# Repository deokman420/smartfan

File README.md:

<h1 align="center">Smartfan</h1>

<p align="center">
  <b>A bathroom fan that knows when to run.</b><br>
  It switches your extractor fan on for light, humidity and odor, runs it until the room is
  actually dry, and then stops. Open source, on a Raspberry Pi Pico 2 W.
</p>

https://github.com/user-attachments/assets/ac6792f2-4697-47a9-bf49-5d41668e7b6c

<p align="center">If the video does not play here, the same walkthrough is in the <a href="https://phbeks.com/blog/smartfan-launch.html">launch write-up</a>.</p>

<p align="center">
  <a href="https://smartfan.phbeks.com"><b>Website</b></a> ·
  <a href="https://smartfan.phbeks.com/demo/"><b>Live demo</b></a> ·
  <a href="https://smartfan.phbeks.com/kb/"><b>Docs</b></a> ·
  <a href="https://my.home-assistant.io/redirect/hacs_repository/?owner=deokman420&repository=smartfan&category=integration"><b>Add to Home Assistant</b></a>
</p>

<p align="center">

</p>

<table>
  <tr>
    <td width="72%"></td>
    <td width="28%"></td>
  </tr>
</table>

<p align="center"><sub>The app, served by the fan itself. <a href="https://smartfan.phbeks.com/demo/">Try it in your browser</a>. The demo starts from four days of real data and simulates a fan from there.</sub></p>

---

## Why another fan controller?

Fixed thresholds don't work in a bathroom.

- **Humidity:** a muggy August day sits at 65 % RH on its own, and a fan set to
  "on above 60 %" never stops. Smartfan learns a slow **baseline** for your room
  and reacts to the **rise** above it.
- **Light:** measured in this room, direct sun reads 85 % of the sensor's range
  and the ceiling lamp 81 %. Daylight is brighter than the bulb, so no level can
  tell them apart. Speed can: the lamp moves the reading 51,511 counts in one
  2-second sample, and the sky never managed more than 51. Smartfan watches for
  that **step**, so sunlight never starts the fan.
- **Odor:** a Sensirion SGP41 reports raw counts with no absolute meaning, and
  they drift with humidity and age. Smartfan learns the room's normal air,
  corrects for humidity, and runs the fan when that changes, **even after the
  light is off**. Then it stops.

A few commercial fans sense odor too. None we found say how theirs decides when
to start or stop. Smartfan's logic is [written down](https://smartfan.phbeks.com/kb/how-it-works/)
and in this repo.

## What it does

|  |  |
|---|---|
| **Runs itself** | Light, humidity and odor start the fan. Humidity decides how long it runs. Run caps stop it running for ever, and stall detection notices a fan that isn't turning. |
| **Its own app, no cloud** | The fan serves its app from its own flash at `http://fan.local/`, with a week of history stored on the board. No account, no server, no broker required. |
| **Home Assistant** | A HACS integration, or MQTT with discovery. Every reading, threshold and control becomes an entity, with a ready-made dashboard. |
| **Signed updates over the air** | Only your build machine can update it, and a bad update rolls itself back. The recovery files only travel over USB. |
| **A button and two lights** | Boost, relearn and Wi-Fi setup all work with no app and no network. |

## In Home Assistant

Add the integration with HACS (custom repository), then add the fan by its
address, `fan.local`. Or point the fan at your MQTT broker and it appears
through discovery. Full guide: [Networking and Home Assistant](https://smartfan.phbeks.com/kb/networking/).

## The hardware

<table>
  <tr>
    <td width="50%"></td>
    <td width="50%"></td>
  </tr>
  <tr>
    <td><b>V1, the bench unit.</b> Running and commissioned in a real bathroom. 5 V USB, no mains anywhere.</td>
    <td><b>V2, the ceiling unit.</b> Designed, not built yet. <a href="https://smartfan.phbeks.com/model/">Explore it in 3D</a>.</td>
  </tr>
</table>

| V1 part | |
|---|---|
| Board | Raspberry Pi Pico 2 W (RP2350), MicroPython 1.29.0 |
| Humidity and temperature | DHT22 |
| Odor | Sensirion SGP41 (VOC and NOx), I²C |
| Light | LDR in a divider against 10 kΩ |
| Fan | Noctua NF-A4x10 5V, 3-wire with tachometer |
| Switching | S8050 NPN, low side |
| Controls | Green and red LEDs, one push button |

Parts, wiring, the pin map and the V2 board are in [Build your own](https://smartfan.phbeks.com/kb/build/).

> [!WARNING]
> **The V2 build in [`hardware/v2/`](hardware/v2/) connects to mains voltage.**
> Mains wiring can kill you and can start a fire. Build it only if you are
> competent to work on mains, keep it unplugged while it is open, and follow
> your local electrical code, which may require a licensed electrician for a
> fixed ceiling installation. The V2 board has **not been fabricated or tested
> yet**. It is a design to check, not a proven build. V1 runs on 5 V USB. This
> project comes with **no warranty** (see [License](#license)).

## Quick start (V1)

You need Python 3 with `pip install mpremote`, Node.js 20+, and a USB cable.
The examples use `COM5`; on Linux or macOS it's something like `/dev/ttyACM0`.

1. **Flash MicroPython**, the Pico 2 W ARM build from
   <https://micropython.org/download/RPI_PICO2_W/>. Hold BOOTSEL, plug in, and
   drag the `.uf2` onto the drive.
2. **Copy the firmware** in safe mode, so the controller and its 8 s watchdog
   aren't running while files land:

   ```bash
   mpremote connect COM5 fs touch :safemode + reset
   mpremote connect COM5 fs cp boot.py ota.py main.py config.py settings.py \
     telemetry.py light.py sgp41.py sht4x.py voc.py net.py mqtt.py ringbuf.py \
     calibrate.py provision.py improv.py httpd.py webapi.py store.py wifi.py :
   ```

   Don't copy `secrets.py`, `settings.json` or `identity.py` from a working
   copy. They belong to one device.
3. **Build and push the app.** This also takes the board out of safe mode:

   ```bash
   cd app && npm ci && cd ..
   python tools/build_www.py --push COM5
   ```

4. **Connect it to Wi-Fi.** With no `secrets.py` the board opens its own setup
   network. See [Set up a unit](https://smartfan.phbeks.com/kb/setup/).
5. **Calibrate the light** in the room it will live in, then optionally add it
   to Home Assistant.

After that, firmware updates go over the air. See
[Updating over the air](https://smartfan.phbeks.com/kb/ota/).

## How it works

| State | Lights | |
|---|---|---|
| LEARN | green blinking | The first 60 s, building the humidity baseline |
| IDLE | green solid | Watching, fan off |
| RUN | red solid | Fan on for light, humidity or odor |
| BOOST | red blinking | A manual 15-minute run |
| FAULT | alternating | A sensor went silent, or the fan isn't turning |

A short press of the button boosts for 15 minutes or clears a fault. Hold it
for two seconds to relearn every baseline, or eight seconds to open the Wi-Fi
setup window.

The control logic, what a real shower looks like, and the field
measurements behind each threshold are in [How it works](https://smartfan.phbeks.com/kb/how-it-works/).

## Documentation

| | |
|---|---|
| [Build your own](https://smartfan.phbeks.com/kb/build/) | Parts, wiring, pin map, first install |
| [Set up a unit](https://smartfan.phbeks.com/kb/setup/) | Wi-Fi provisioning, naming, calibration |
| [Networking and Home Assistant](https://smartfan.phbeks.com/kb/networking/) | The fan's own server, MQTT, the dashboard |
| [Updating over the air](https://smartfan.phbeks.com/kb/ota/) | Signed OTA, and why it can't brick the board |
| [How it works](https://smartfan.phbeks.com/kb/how-it-works/) | States, control logic, a real shower |
| [Odor sensing with the SGP41](https://smartfan.phbeks.com/kb/sgp41-odor-sensing/) | The signal, its sign, and settling time |
| [Daylight is brighter than the bulb](https://smartfan.phbeks.com/kb/daylight-is-brighter-than-the-bulb/) | Why light is found by its step, not its level |
| [Files in the repo](https://smartfan.phbeks.com/kb/files/) | What each file does |
| [Roadmap](https://smartfan.phbeks.com/kb/roadmap/) | The phases so far, the ceiling unit and multi-room next |

The same pages are in [`docs/`](docs/) if you'd rather read them here.

## Repository layout

| Path | What's in it |
|---|---|
| `*.py` (root) | The MicroPython firmware: control loop, sensors, Wi-Fi, HTTP API, OTA |
| [`app/`](app/) | The Svelte app the fan serves, plus the public demo build |
| [`custom_components/smartfan/`](custom_components/smartfan/) | The Home Assistant integration |
| [`hardware/`](hardware/) | V2 schematic, PCB and printed parts (build123d scripts and STLs) |
| [`tools/`](tools/) | Build, flash, OTA publishing and dashboard scripts |
| [`tests/`](tests/) | Regression suites, from host-only checks to hardware and HA |
| [`docs/`](docs/), [`site/`](site/) | The knowledge base and the website at smartfan.phbeks.com |

## Contributing

Issues and pull requests are welcome. Before opening a pull request:

- Run the host-only suites listed in [`tests/README.md`](tests/README.md). They
  need no board.
- Write in American English (color, not colour), in code, docs and UI text.
- Keep a behavior change and its doc change in the same commit. The docs live
  in this repo for that reason.

## License

- **Firmware, app, Home Assistant integration and tools:** GNU GPL v3.0. See
  [`LICENSE`](LICENSE).
- **Hardware** (everything in [`hardware/`](hardware/): schematic, PCB,
  Gerbers, CAD scripts and STLs): CERN Open Hardware Licence v2, Strongly
  Reciprocal. See [`hardware/LICENSE`](hardware/LICENSE).
- **Bundled third-party files** keep their own licenses: Inter and JetBrains
  Mono (SIL Open Font License, [`app/LICENSES/`](app/LICENSES/)) and three.js
  (MIT, [`hardware/v2/cad/vendor/LICENSE-three.txt`](hardware/v2/cad/vendor/LICENSE-three.txt)).

Both licenses come with no warranty. You build and install this at your own
risk, and that matters most for anything connected to mains.

<p align="center"><sub>Made by <a href="https://phbeks.com">phbeks.com</a></sub></p>

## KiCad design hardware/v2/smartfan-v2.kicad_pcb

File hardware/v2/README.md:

# Smartfan V2 board

> [!WARNING]
> **Not fabricated, not tested, and it carries mains.** Nothing here has been built yet. Check every footprint against parts in hand (see "Before fab" below) before ordering, and do not power it from mains unless you are competent to work on mains. Licensed under CERN-OHL-S v2 ([`../LICENSE`](../LICENSE)), with no warranty.

Schematic and PCB for prototype V2: one Noctua NF-F12, a Pico 2 W, and an SHT40. This is not the two-fan V2.2 board. The circuit is described in `hardware/v2/prototype-v2.md`, `hardware/v2/build-sheet-v2.html` and `hardware/v2/wiring-v2.html`. The board changed that circuit in three ways, listed under "Changed on 2026-11-08", and those files were brought in line on 2026-11-09. Where they disagree with this README, this README wins.

Open `smartfan-v2.kicad_pro` in KiCad 10. `generate.py` is the source. It rewrites the schematic and the board. Run it with KiCad's Python:

```
& "$env:LOCALAPPDATA\Programs\KiCad\10.0\bin\python.exe" hardware/v2/generate.py
```

Do not hand-edit `smartfan-v2.kicad_sch`, `smartfan-v2.kicad_pcb` or `smartfan-v2.kicad_dru`.

The run checks itself and stops on the first problem:

1. The netlist KiCad reads from the drawn schematic must match `PARTS` pin for pin, the off-board parts included.
2. ERC. The only findings allowed are `lib_symbol_mismatch` warnings, because the symbols are embedded, renamed copies.
3. DRC with schematic parity. It has to come back empty.

Then it rewrites `smartfan-v2-schematic.pdf`, `smartfan-v2-front.svg` (front copper and silk), `smartfan-v2-back.svg` (back copper, same orientation as the front, so the ground pour and the +12 V / +5 V runs are visible) and everything in `fab/`. On 2026-11-08 in KiCad 10.0.5: 24 `lib_symbol_mismatch` warnings, DRC clean, parity clean.

`fab/` holds the Gerbers and the drill files. Two layers, 1.6 mm, 1 oz copper. The plot origin is the lower-left corner of the outline, in millimeters, and the coordinates are positive. The plated holes, and the one via, are in `smartfan-v2-PTH.drl`. `smartfan-v2-NPTH.drl` has the MOSFET tab hole (3.5 mm) and the fan header's locating peg (1.1 mm). The four mounting holes are unplated 3.2 mm circles in `smartfan-v2-Edge_Cuts.gm1`, not in the drill file. The back silkscreen is empty.

## Mains

120 V lands in J5, a Phoenix MKDS 1,5/2-5,08 screw terminal (1715721) beside the IRM-10's AC pins. Its wire entries face the mains end wall. Pin 1 takes the C8's unfused lead. Pin 2 takes the lead from the fuse holder. The C8 is not polarized, so "hot" means whichever lead the fuse is in. The silk says C8 and FUSE. The IEC C8 and the fuse holder are panel parts. They are on the schematic and not on the board.

There is no earth. Do not bond 0 V or the MOSFET tab to the box. The tab is the drain: use no screw in it, or a nylon one. If the module marks and the schematic disagree on which pin is +12 V, follow the module.

120 V copper keeps 6.4 mm from everything that is not 120 V. That is more than reinforced insulation needs at 120 V, and enough at 230 V.

- The DRC rule in `smartfan-v2.kicad_dru` enforces it as both clearance and creepage. It covers low-voltage copper, the ground pour, and pads with no net.
- DRC checks one copper layer at a time. `generate.py` also keeps 6.4 mm between layers, which DRC does not check.
- The closest approach is 6.50 mm, between the fused lead and the back ground pour.
- Line to neutral is 2.48 mm at J5's own pads and 3 mm or more elsewhere.
- A screw head or hex standoff at the nearest mounting hole is 8.3 mm from 120 V copper.

## Before fab

None of this has been checked against parts in hand. Do it before ordering.

1. **Wi-Fi in a closed aluminum box.** An unpainted die-cast 1590BB with the lid on is close to a shielded can. The Pico's only antenna is on the module, and the whole unit runs over Wi-Fi: MQTT, Home Assistant and OTA. Put a running Pico W, or a phone, in the box with the lid screwed down, and read the signal from the router or `/api/state`. If it drops out, the fix is a plastic lid or a plastic window over the antenna. That changes the box, not the board, but it decides whether this box is the right one. The board keeps all copper off both layers under the antenna and for 7 mm past the end of the module.
2. **Caliper the box.** The 96 × 70 mm outline uses Hammond's drawing figures: a flat of 103.50 × 78.00 mm between the corner bosses and a 29.75 mm inner height. Stacking 21.5 mm for the IRM-10 and 1.6 mm of board leaves 6.6 mm for standoffs with nothing to spare. Use 5 or 6 mm nylon standoffs.
3. **Insulate under the board.** The 120 V solder joints face the aluminum floor about 4 mm away. Lay a 0.4 mm polycarbonate or fish-paper sheet under the board, and trim the AC leads short.
4. **Panel parts against the board.** The C8 inlet and the fuse holder reach roughly 20–35 mm into the box from the mains end wall. The board covers most of the floor, and the IRM-10 at that end is 21.5 mm tall. Check, with the parts in the box, that neither one lands on the module or on J5's screws.
5. **Print the board 1:1 and lay the parts on it.** Check the IRM-10 pins, the R-78E, J5, the keyed fan header, and the Pico sockets.
6. **USB faces the mains end.** The build sheet puts a USB slot in the far wall, but on this board the Pico's USB end is at the mains end, beside J5. With the board in the box, unplug the cord, take the lid off, and use a right-angle micro-USB lead, or lift the Pico out of its sockets. The `www/` bundle only goes over USB.

## Changed on 2026-11-08

- **J5, the mains terminal**, is new. Before, the C8 and fuse leads were to be soldered to the IRM-10's pins on the underside, with no strain relief and facing the floor. The mounting hole at (12, 34) moved to (22, 33.5) to make room.
- **J2 is a keyed 4-pin fan header** (`FanPinHeader_1x04`; Molex 47053-1000 or any 4-pin PWM fan header). A bare pin header let the fan plug go on backwards. That puts switched 12 V on the fan's tach output and the fan's ground on +5 V.
- **The LED resistors moved to the anode side**, and **R9, 1 kΩ, is new** in series with the button. R7, R8 and R9 now sit between J4 and the Pico. A pinched grille cable, or a static spark at the button, now meets a resistor before it meets a GPIO. J4's pinout is unchanged; pins 4 and 6 are ground on the board.
- **The fan switch was regrouped** around Q1:
  - R4 runs from gate to source on the left of Q1.
  - R3 drops straight from the gate to Q2's collector.
  - R1 and R2 meet the base from below and above.
  - D2 hangs off the yellow lead.
  - R5 sits over the tach pin.
  - J4 moved beside J2.

  The holes at (80, 32) and (76, 50) moved to (80, 36.5) and (91, 63). Every net in that corner is a short hand route. The tach line crosses the fan line on the back and comes up through one via. The old board's router walked BASE 120 mm, FAN_ON 118 mm and LIGHT 317 mm. Now they are 24, 7 and 44 mm.
- **R6** sits beside J3, so the LDR line no longer crosses the board.
- **Net names and footprint library names** on the board now match the schematic. "Update PCB from Schematic" no longer renames every net or swaps every footprint.
- **The schematic** joins the Pico by labels instead of long wires, places every reference and value clear of wires, and marks junctions.

## Wiring the connectors

J2 is the NF-F12, pin 1 at the square pad. The keying wall faces the board edge. The silk names each lead's color.

1. Black, permanent 0 V. Do not low-side switch it.
2. Yellow, IRF9540 drain, switched +12 V. Never a GPIO.
3. Green, open-collector tach to GP18, pulled up to Pico 3V3 only.
4. Blue, +5 V from the buck, before the 1N5819. Never 12 V and never VSYS. A low PWM pin stops the fan even with 12 V on yellow.

These are not the V1 lead colors. On the V1 NF-A4x10, yellow was tach.

J3 is the grille sensor cable, six pins: 1 GND, 2 3V3, 3 SDA (GP0), 4 SCL (GP1), 5 LDR, 6 3V3 for the LDR. Pull-ups are on the SHT40. R6 stays on the board. SGP41 is not on this board. GP22 is free. The DHT22 does not come across.

J4 is the button and LED cable, six pins: 1 GND, 2 button, 3 green anode, 4 green cathode, 5 red anode, 6 red cathode. The button reaches GP16 through R9, the green LED GP19 through R7, the red LED GP20 through R8. The button, both LEDs, the LDR and the SHT40 are on the grille, not on this board.

J5 is mains: pin 1 the C8's unfused lead, pin 2 from the fuse.

## The rest

- The Pico sits in two 20-pin sockets. The footprint assumes it, and traces run under the module.
- VBUS, pin 40, gets no wire. Installed power is the buck into VSYS, pin 39, through the 1N5819. The band is the cathode at VSYS. With the cord in and USB unplugged, pin 39 should read about 4.5–4.8 V.
- GP17 high turns the fan on. R1, 1 kΩ, is the base resistor. R2, 100 kΩ, holds the base down while GP17 floats at boot. Do not swap them. The S8050 flat face, left to right, is E-B-C. Diode-test it before soldering.
- The Recom R-78E5.0-1.0 uses the 0.5 A footprint. The pin pitch matches. The body is 11.6 × 8.5 × 10.4 mm. Its datasheet needs no external capacitors; 10 µF on the input is only part of its EMC filter.
- The grille parts are drawn off the board and connect through J3 and J4. On the schematic, labels with the same name are one net.

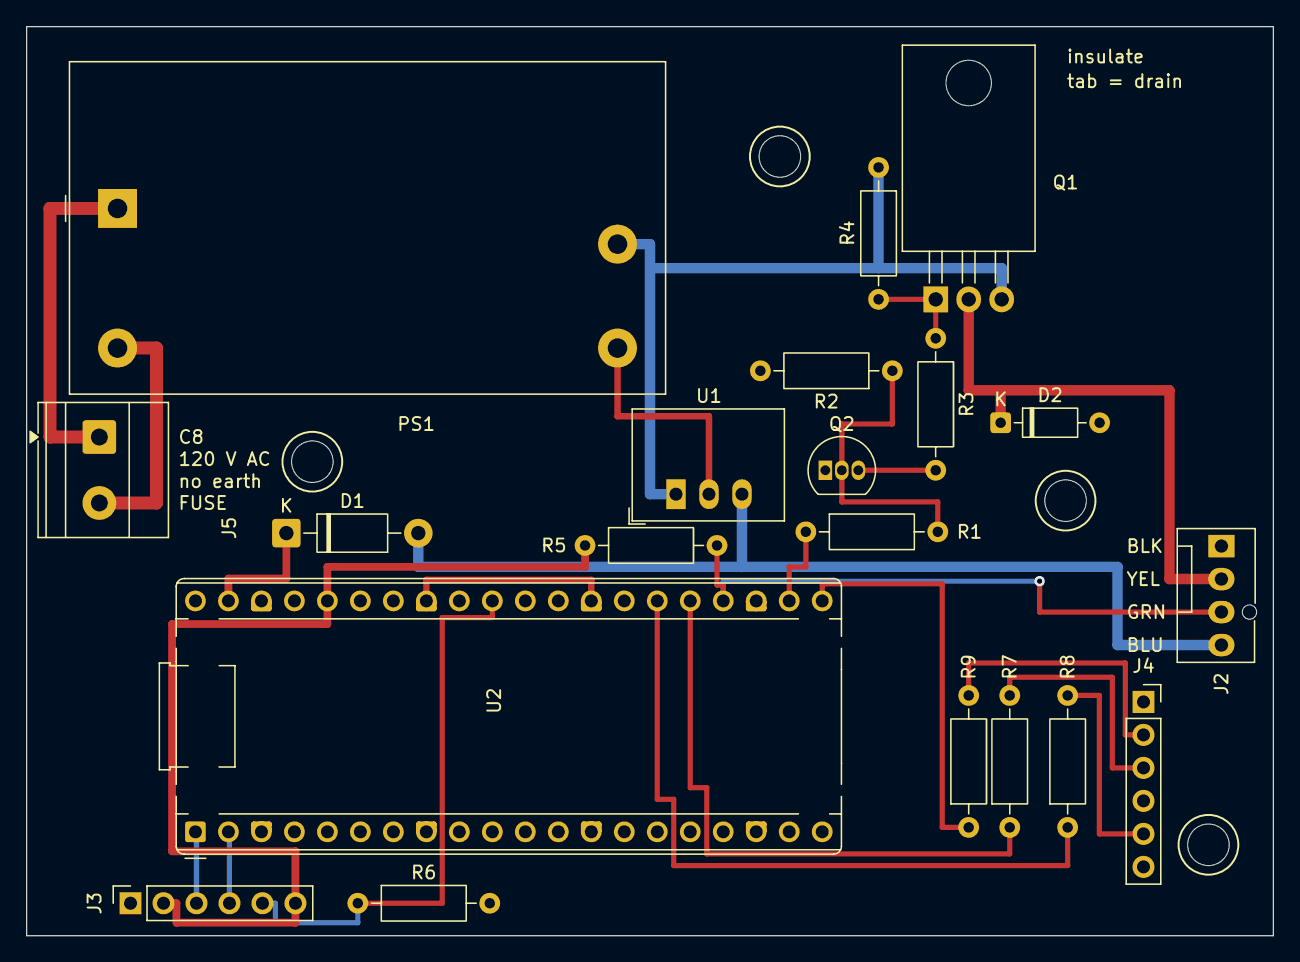
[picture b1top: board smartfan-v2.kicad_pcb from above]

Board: 2 copper layers, 96.0 x 70.0 mm, 20 parts (0 on the bottom side), 22 nets.

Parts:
D1: 1N5819; D_DO-41_SOD81_P10.16mm_Horizontal
D2: 1N4148; D_DO-35_SOD27_P7.62mm_Horizontal
J2: NF-F12 fan; FanPinHeader_1x04_P2.54mm_Vertical
J3: grille sensors; PinSocket_1x06_P2.54mm_Vertical
J4: button + LEDs; PinSocket_1x06_P2.54mm_Vertical
J5: AC in; TerminalBlock_Phoenix_MKDS-1,5-2-5.08_1x02_P5.08mm_Horizont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
PS1: IRM-10-12; Converter_ACDC_MeanWell_IRM-10-xx_THT
Q1: IRF9540NPBF; TO-220-3_Horizontal_TabDown
Q2: S8050; TO-92_Inline
R1, R9: 1k; R_Axial_DIN0207_L6.3mm_D2.5mm_P10.16mm_Horizontal
R2, R4: 100k; R_Axial_DIN0207_L6.3mm_D2.5mm_P10.16mm_Horizontal
R3: 100; R_Axial_DIN0207_L6.3mm_D2.5mm_P10.16mm_Horizontal
R5, R6: 10k; R_Axial_DIN0207_L6.3mm_D2.5mm_P10.16mm_Horizontal
R7, R8: 330; R_Axial_DIN0207_L6.3mm_D2.5mm_P10.16mm_Horizontal
U1: R-78E5.0-1.0; Converter_DCDC_RECOM_R-78E-0.5_THT
U2: Pico 2 W; RaspberryPi_Pico_Common_THT

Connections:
+3.3V: J3.2, J3.6, R5.1, U2.36
+5V: D1.2, J2.4, U1.3
+12V: PS1.4, Q1.3, R4.1, U1.1
/AC_HOT: J5.2, PS1.2
/AC_N: J5.1, PS1.1
/BASE: Q2.2, R1.2, R2.1
/BTN: R9.1, U2.21
/COLL: Q2.3, R3.2
/FAN_ON: R1.1, U2.22
/GATE: Q1.1, R3.1, R4.2
/J4_BTN: J4.2, R9.2
/J4_GREEN: J4.3, R7.2
/J4_RED: J4.5, R8.2
/LED_OK: R7.1, U2.25
/LED_RUN: R8.1, U2.26
/LIGHT: J3.5, R6.1, U2.31
/SCL: J3.4, U2.2
/SDA: J3.3, U2.1
/TACH: J2.3, R5.2, U2.24
/VSYS: D1.1, U2.39
/YELLOW: D2.1, J2.2, Q1.2
GND: D2.2, J2.1, J3.1, J4.1, J4.4, J4.6, PS1.3, Q2.1, R2.2, R6.2, U1.2, U2.3, U2.8, U2.13, U2.18, U2.23, U2.28, U2.33, U2.38

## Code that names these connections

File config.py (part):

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PIN_DHT     = 22   # DHT22 data, 10k pull-up to 3V3
PIN_LDR     = 26   # ADC0, top of the LDR divider
PIN_BUTTON  = 16   # to GND, internal pull-up
PIN_FAN     = 17   # 1k to S8050 base
PIN_TACH    = 18   # fan yellow, 10k pull-up to 3V3
PIN_LED_OK  = 19   # green
PIN_LED_RUN = 20   # red

# --- Light sensing --------------------------------------------------
# Raw ADC, 0-65535. Bright reads high.
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                 # still catches a seized bearing or a severed lead. This is
                 # the only thing that notices a fan that has died in the
                 # ceiling. Set to 0 to disable.
SPINUP_S = 3     # ignore the tach while the fan gets going

# A fan still turning well after it was told to stop is not a slow coast --
# it means the switch is not in control of it. The usual cause is the fan's
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# for it, which could be days. This drives the fan briefly at boot so the
# question is asked at a moment somebody is present to hear the answer.
#
# Long enough to clear SPINUP_S and then measure a real tach window, which
# is one SAMPLE_S. Set to 0 to disable.
SELFTEST_S = 6

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

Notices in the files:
README.md:
License: GPL v3
Hardware: CERN-OHL-S v2
